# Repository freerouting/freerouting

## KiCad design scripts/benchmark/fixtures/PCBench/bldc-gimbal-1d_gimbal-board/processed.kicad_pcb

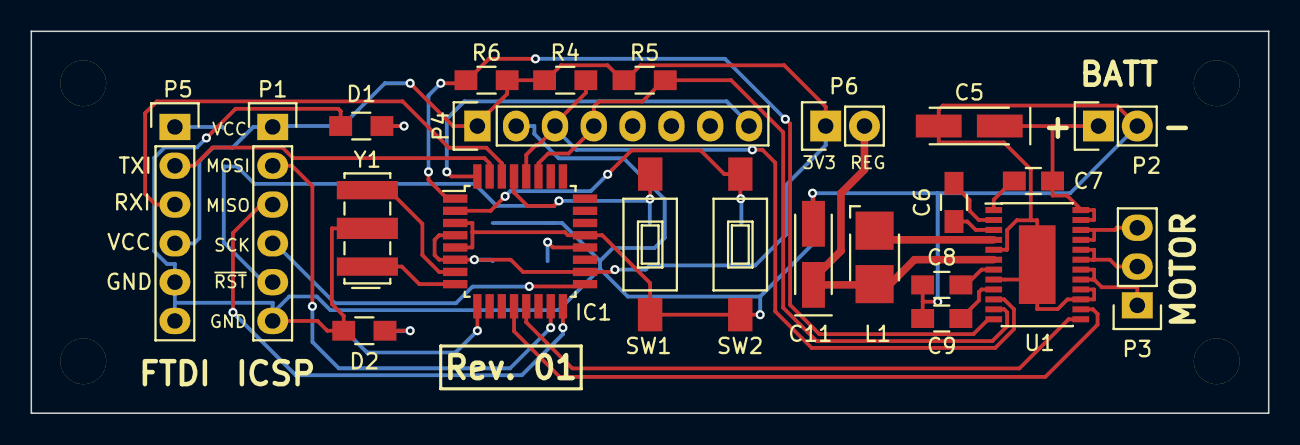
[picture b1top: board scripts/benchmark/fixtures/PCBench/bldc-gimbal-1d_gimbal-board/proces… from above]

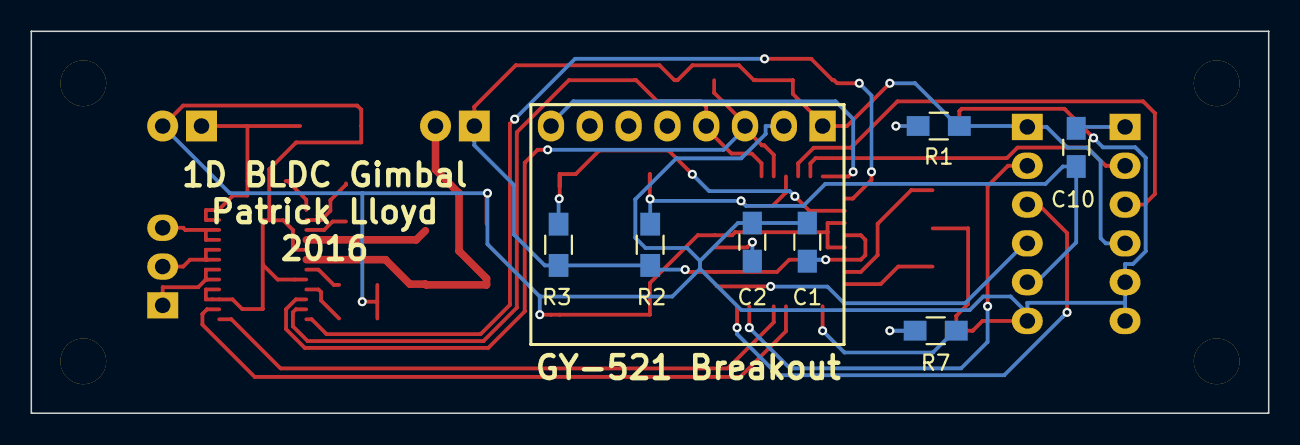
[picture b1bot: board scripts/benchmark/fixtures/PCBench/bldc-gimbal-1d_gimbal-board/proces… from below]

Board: 2 copper layers, 81.0 x 25.0 mm, 34 parts (7 on the bottom side), 33 nets.

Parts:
C1, C2, C6, C7, C10: 0.1uF; C_0805_HandSoldering
C5, C11: 10uF; TantalC_SizeA_EIA-3216_HandSoldering
C8, C9: 1uF; C_0805_HandSoldering
D1: RED; R_0805_HandSoldering
D2: GRN; R_0805_HandSoldering
H1, H2, H3, H4: CONN_01X01; MountingHole_3mm
IC1: ATMEGA328P-A; TQFP-32_7x7mm_Pitch0.8mm
L1: 47uH; Inductor_1212
P1: ICSP; Pin_Header_Straight_1x06
P2: BATT; Pin_Header_Straight_1x02
P3: MOTOR; Pin_Header_Straight_1x03
P4: IMU; Pin_Header_Straight_1x08
P5: FTDI; Pin_Header_Straight_1x06
P6: 3V3_CONN; Pin_Header_Straight_1x02
R1, R7: 330; R_0805_HandSoldering
R2, R3: 10K; R_0805_HandSoldering
R4, R5, R6: DNP; R_0805_HandSoldering
SW1, SW2: SW_PUSH; SW_SPST_FSMSM
U1: DRV10975; TSSOP-24_4.4x7.8mm_Pitch0.65mm_EP
Y1: Resonator; Resonator_7.2x3mm

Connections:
+3V3: C1.1, IC1.4, IC1.6, IC1.18, P1.1, P4.1, P5.4, P6.1, R1.1, R2.2, R3.2, R4.1, R5.1, R6.1
+BATT: C5.1, C7.2, P2.1, U1.23, U1.24
/ICSP_MISO: IC1.16, P1.3
/ICSP_MOSI: IC1.15, P1.2
/ICSP_SCK: IC1.17, P1.4
/IMU_INT: IC1.32, P4.8
/M_DIR: IC1.12, U1.14
/M_FG: IC1.1, R6.2, U1.12
/M_PHASE_U: P3.1, U1.17, U1.18
/M_PHASE_V: P3.2, U1.19, U1.20
/M_PHASE_W: P3.3, U1.21, U1.22
/M_SPEED: IC1.13, U1.13
/REG_OUT: C11.1, L1.2, P6.2, U1.6
/RESET: C10.1, IC1.29, P1.5, R2.1, SW1.1
/SCL: IC1.28, P4.3, R4.2, U1.10
/SDA: IC1.27, P4.4, R5.2, U1.11
/USART_DTR: C10.2, P5.1
/USART_RX: IC1.30, P5.3
/USART_TX: IC1.31, P5.2
/V3P3: C9.1, U1.9
GND: C1.2, C2.2, C5.2, C8.2, C9.2, C11.2, D1.1, D2.1, IC1.3, IC1.5, IC1.21, P1.6, P2.2, P4.2, P5.5, P5.6, SW1.2, SW2.2, U1.5, U1.8, U1.15, U1.16, U1.EP, Y1.2
unnamed: C2.1, IC1.20
unnamed: C6.1, U1.3
unnamed: C6.2, U1.2
unnamed: C7.1, U1.1
unnamed: C8.1, U1.7
unnamed: D1.2, R1.2
unnamed: D2.2, R7.2
unnamed: IC1.2, R3.1, SW2.1
unnamed: IC1.7, Y1.3
unnamed: IC1.8, Y1.1
unnamed: IC1.9, R7.1
unnamed: L1.1, U1.4

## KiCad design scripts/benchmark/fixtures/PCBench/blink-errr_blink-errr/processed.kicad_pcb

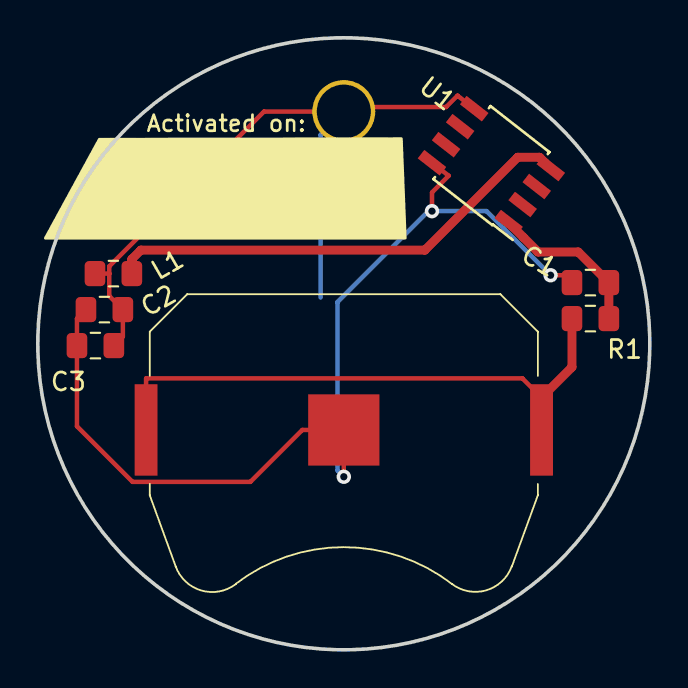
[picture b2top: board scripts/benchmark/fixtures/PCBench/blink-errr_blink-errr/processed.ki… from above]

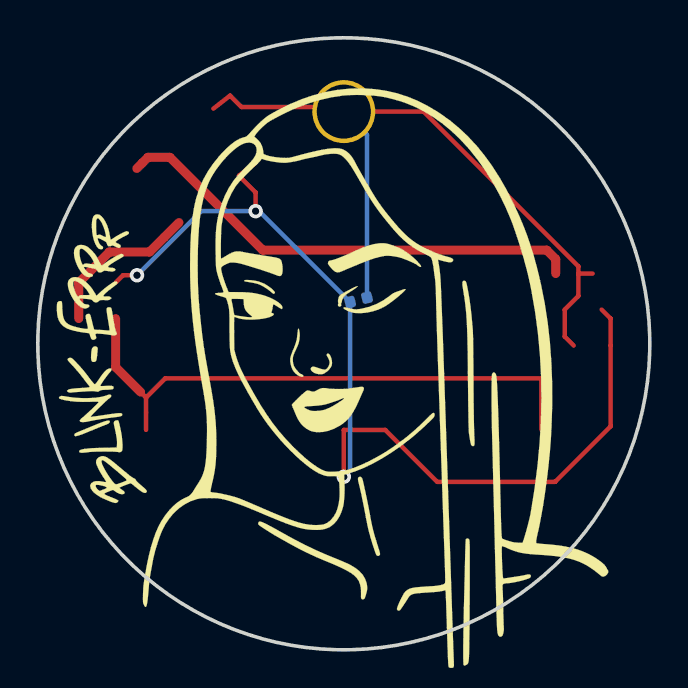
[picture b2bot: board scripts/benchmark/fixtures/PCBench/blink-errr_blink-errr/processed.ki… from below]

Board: 2 copper layers, 34.0 x 34.0 mm, 9 parts (2 on the bottom side), 5 nets.

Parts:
BT1: Battery_Cell; BatteryHolder_Keystone_3034_1x20mm
C1, C2, C3: C; C_0805_2012Metric_Pad1.15x1.40mm_HandSolder
D1: LED; LED_0402_1005Metric
H1: MountingHole; MountingHole_3.2mm_M3_DIN965_Pad
L1: L; L_0805_2012Metric_Pad1.15x1.40mm_HandSolder
R1: R; R_0805_2012Metric_Pad1.15x1.40mm_HandSolder
U1: ATtiny202-SS; SOIC-8_3.9x4.9mm_P1.27mm

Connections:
FEEDBACK: C2.1, C3.1, D1.2, H1.1, L1.2, U1.5
GND: BT1.2, C1.2, C2.2, C3.2, D1.1, U1.8
unnamed: BT1.1, R1.2
unnamed: L1.1, U1.4
VCC: C1.1, R1.1, U1.1
